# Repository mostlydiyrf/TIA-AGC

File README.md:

# TIA-AGC
A termination-insensitive IF amplifier with AGC.

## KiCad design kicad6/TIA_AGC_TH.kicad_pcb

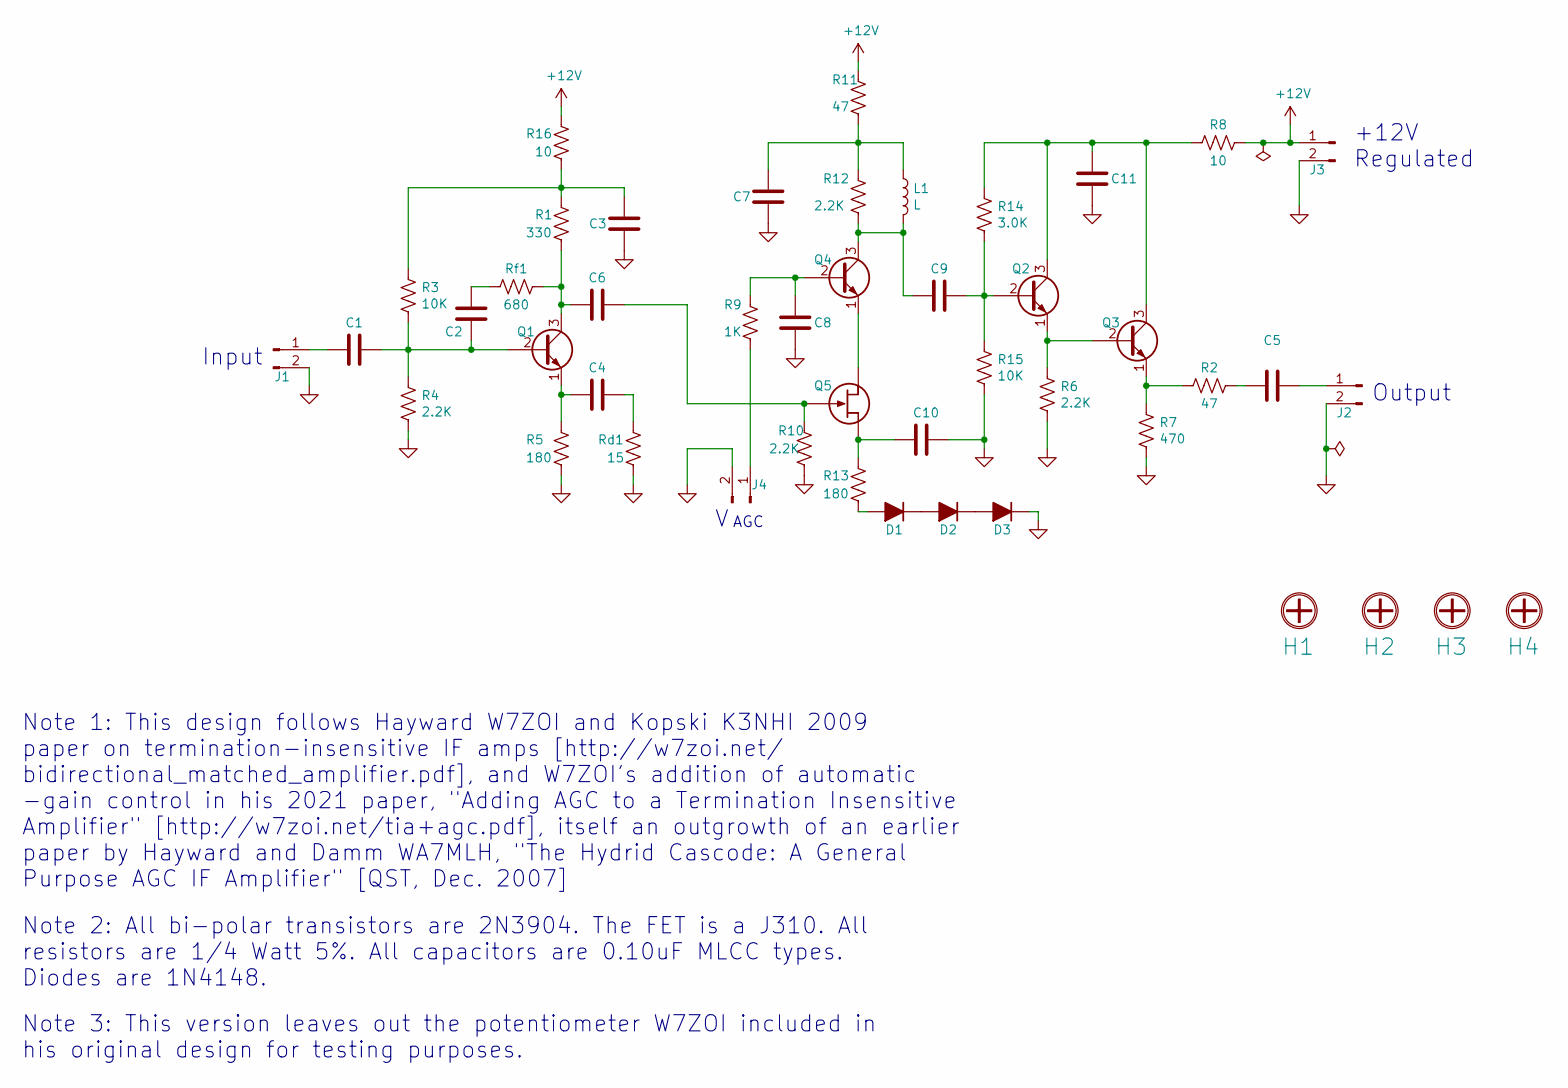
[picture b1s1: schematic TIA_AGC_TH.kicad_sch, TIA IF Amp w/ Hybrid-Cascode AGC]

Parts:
C1, C2, C3, C4, C5, C6, C7, C8, C9, C10, C11: 0.10; Ceramic_Disk_Capacitor_P5.00mm
D1, D2, D3: D; D_DO-35_SOD27_P5.08mm_Vertical_KathodeUp
H1, H2, H3, H4: Mounting_Hole_4-40; MountingHole_3.2mm_M3_Pad
J1, J2: Conn_01x02_Male; SMA_EdgeMount_0.062_Samtec
J3, J4: Conn_01x02_Male; PinHeader_1x02_P2.54mm_Vertical
L1: L; R_Axial_DIN0207_L6.3mm_D2.5mm_P5.08mm_Vertical
Q1, Q2, Q3, Q4: 2N3904; TO-92L_Pin2_Offset
Q5: J310; TO-92L_Pin2_Offset
R1: 330; R_Axial_DIN0207_L6.3mm_D2.5mm_P5.08mm_Vertical
R2, R11: 47; R_Axial_DIN0207_L6.3mm_D2.5mm_P5.08mm_Vertical
R3, R15: 10K; R_Axial_DIN0207_L6.3mm_D2.5mm_P5.08mm_Vertical
R4, R6, R10, R12: 2.2K; R_Axial_DIN0207_L6.3mm_D2.5mm_P5.08mm_Vertical
R5, R13: 180; R_Axial_DIN0207_L6.3mm_D2.5mm_P5.08mm_Vertical
R7: 470; R_Axial_DIN0207_L6.3mm_D2.5mm_P5.08mm_Vertical
R8, R16: 10; R_Axial_DIN0207_L6.3mm_D2.5mm_P5.08mm_Vertical
R9: 1K; R_Axial_DIN0207_L6.3mm_D2.5mm_P5.08mm_Vertical
R14: 3.0K; R_Axial_DIN0207_L6.3mm_D2.5mm_P5.08mm_Vertical
Rd1: 15; R_Axial_DIN0207_L6.3mm_D2.5mm_P5.08mm_Vertical
Rf1: 680; R_Axial_DIN0207_L6.3mm_D2.5mm_P5.08mm_Vertical

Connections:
+12V: J3.1, R8.1, R11.1, R16.1
GND: C3.1, C7.1, C8.1, C10.2, C11.1, D3.1 (K), J1.2, J2.2, J3.2, J4.2, R4.2, R5.2, R6.2, R7.2, R10.2, R15.2, Rd1.2
unnamed: C1.1, C2.1, Q1.2 (B), R3.2, R4.1
unnamed: C1.2, J1.1
unnamed: C2.2, Rf1.2
unnamed: C3.2, R1.1, R3.1, R16.2
unnamed: C4.1, Rd1.1
unnamed: C4.2, Q1.1 (E), R5.1
unnamed: C5.1, J2.1
unnamed: C5.2, R2.1
unnamed: C6.1, Q5.3 (G), R10.1
unnamed: C6.2, Q1.3 (C), R1.2, Rf1.1
unnamed: C7.2, L1.1, R11.2, R12.1
unnamed: C8.2, Q4.2 (B), R9.1
unnamed: C9.1, Q2.2 (B), R14.2, R15.1
unnamed: C9.2, L1.2, Q4.3 (C), R12.2
unnamed: C10.1, Q5.2 (S), R13.1
unnamed: C11.2, Q2.3 (C), Q3.3 (C), R8.2, R14.1
unnamed: D1.1 (K), D2.2 (A)
unnamed: D1.2 (A), R13.2
unnamed: D2.1 (K), D3.2 (A)
unnamed: J4.1, R9.2
unnamed: Q2.1 (E), Q3.2 (B), R6.1
unnamed: Q3.1 (E), R2.2, R7.1
unnamed: Q4.1 (E), Q5.1 (D)

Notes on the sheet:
Input
Note 3: This version leaves out the potentiometer W7ZOI included in his original design for testing purposes.
Note 2: All bi-polar transistors are 2N3904. The FET is a J310. All resistors are 1/4 Watt 5%. All capacitors are 0.10uF MLCC types. Diodes are 1N4148.
Note 1: This design follows Hayward W7ZOI and Kopski K3NHI 2009 paper on termination-insensitive IF amps [http://w7zoi.net/ bidirectional_matched_amplifier.pdf], and W7ZOI's addition of automatic -gain control in his 2021 paper, "Adding AGC to a Termination Insensitive Amplifier" [http://w7zoi.net/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
AGC
+12V Regulated
Output

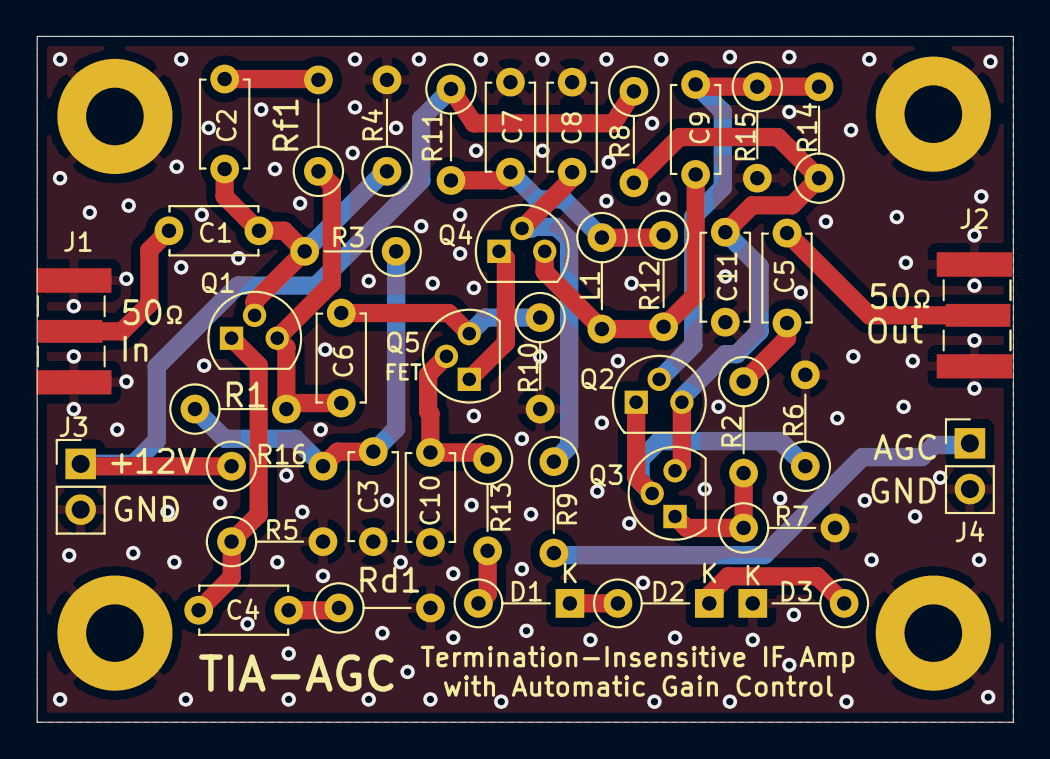
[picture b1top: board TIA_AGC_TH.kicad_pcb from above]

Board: 2 copper layers, 54.2 x 38.1 mm, 46 parts (0 on the bottom side), 25 nets.
